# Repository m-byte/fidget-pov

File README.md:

# fidgethw
https://hackaday.io/project/25372-iot-pov-fidget-spinner

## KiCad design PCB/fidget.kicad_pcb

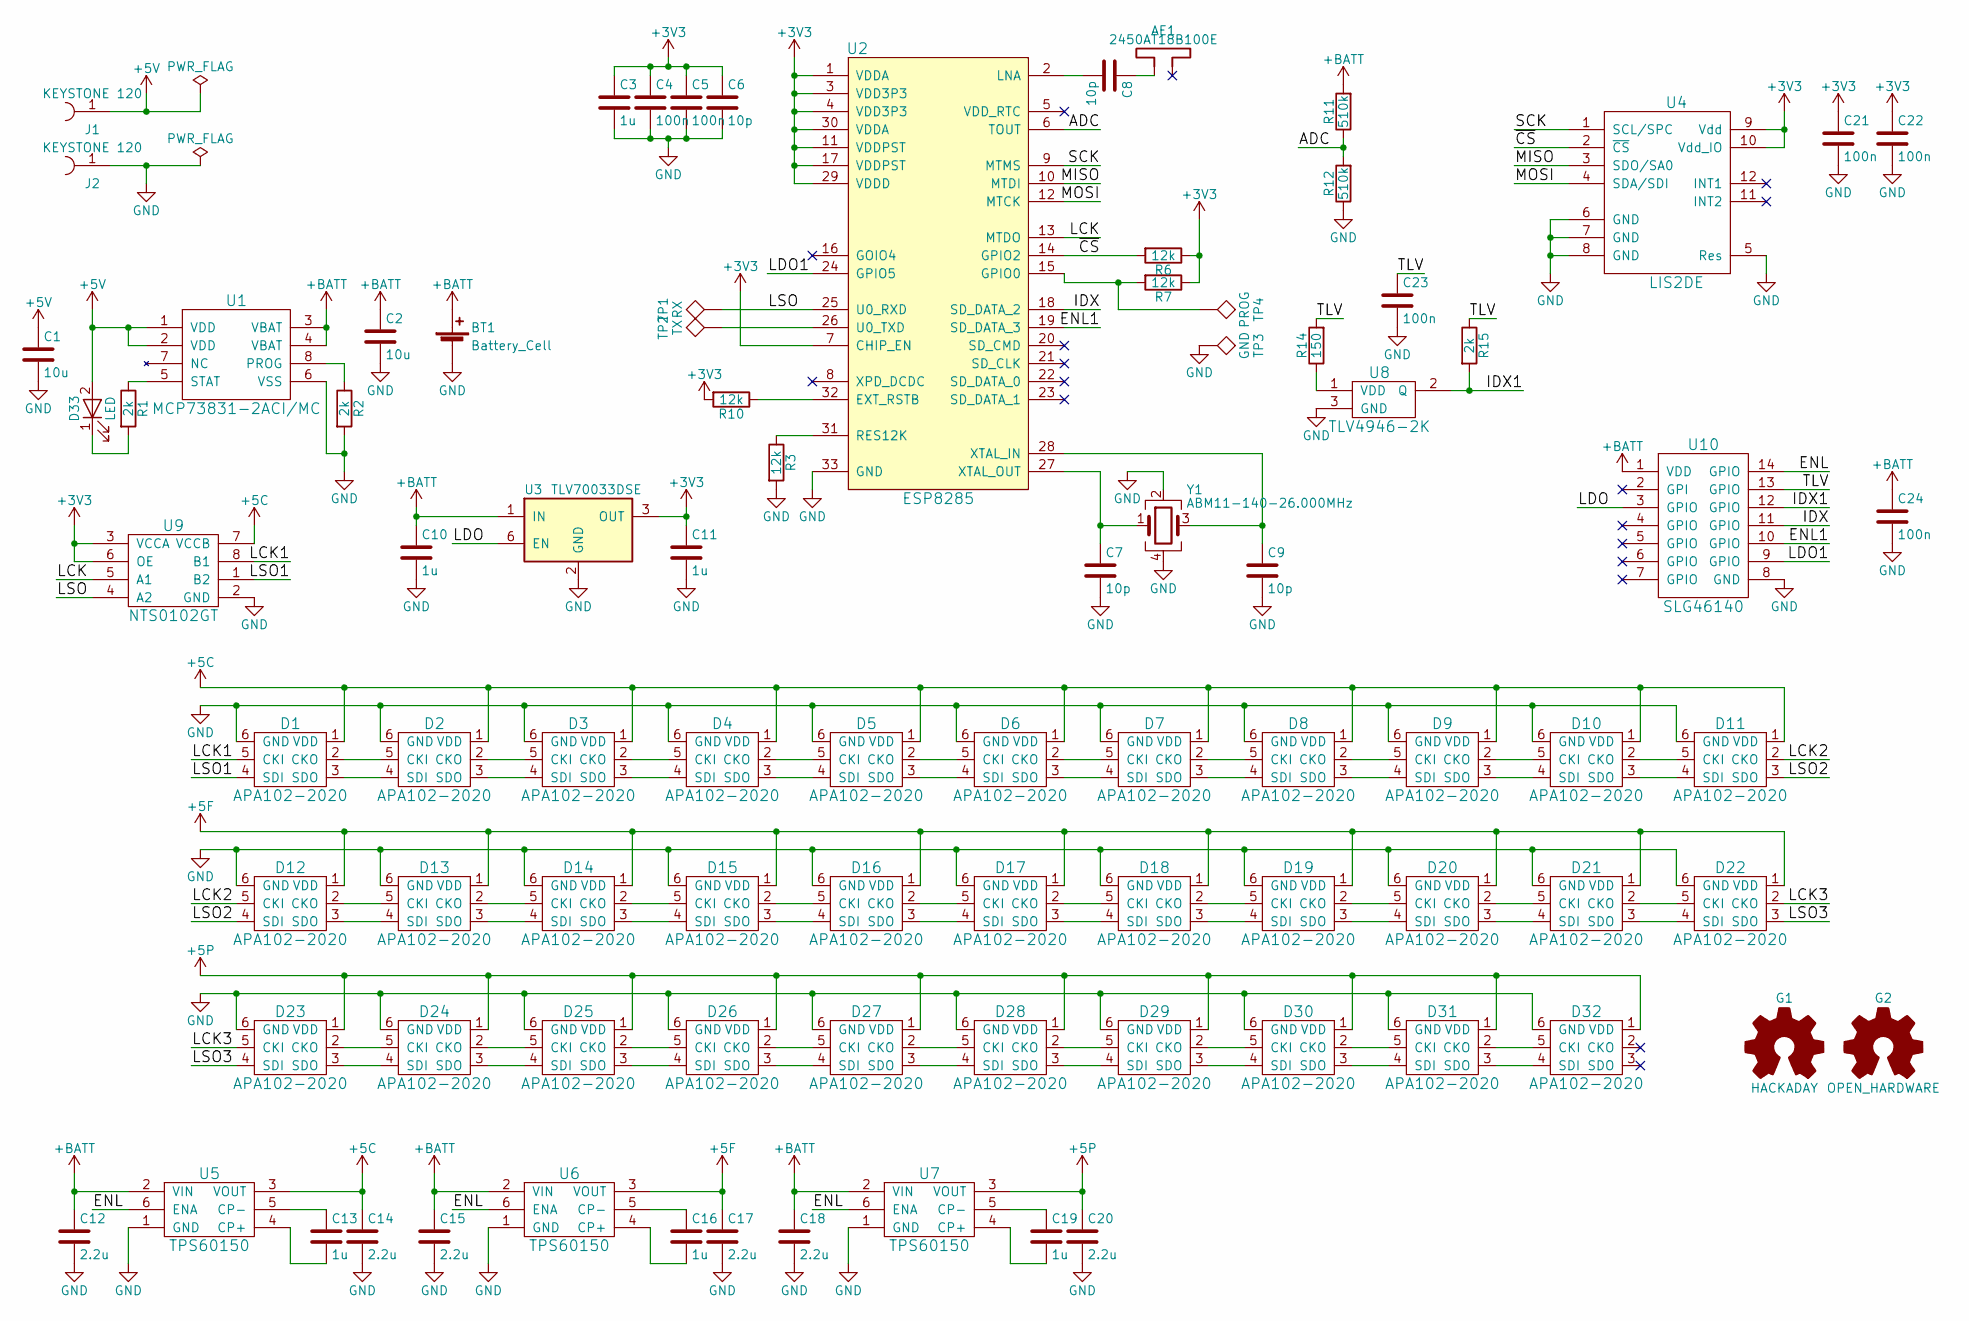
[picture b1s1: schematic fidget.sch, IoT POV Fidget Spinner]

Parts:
AE1: 2450AT18B100E; SMD-1206_Pol
BT1: Battery_Cell; Pin_Header_Straight_1x02_Pitch2.00mm
C1, C2: 10u; C_0603
C3, C10, C11: 1u; C_0402
C4, C5, C21, C22, C23, C24: 100n; C_0402
C6, C7, C8, C9: 10p; C_0402
C12, C14, C15, C17, C18, C20: 2.2u; C_0603
C13, C16, C19: 1u; C_0603
D1, D2, D3, D4, D5, D6, D7, D8, D9, D10, D11, D12, D13, D14, D15, D16, D17, D18, D19, D20, D21, D22, D23, D24, D25, D26, D27, D28, D29, D30, D31, D32: APA102-2020; LED_APA102-2020
D33: LED; LED_0805
G1: HACKADAY; wrencher_8mm
G2: OPEN_HARDWARE; OSHW-Logo_7.5x8mm_SilkScreen
J1, J2: KEYSTONE 120; Keystone_120_19mm
R1, R2, R15: 2k; R_0402
R3, R6, R7, R10: 12k; R_0402
R11, R12: 510k; R_0402
R14: 150; R_0402
TP1: RX; Measurement_Point_Round-SMD-Pad_Small
TP2: TX; Measurement_Point_Round-SMD-Pad_Small
TP3: GND; Measurement_Point_Round-SMD-Pad_Small
TP4: PROG; Measurement_Point_Round-SMD-Pad_Small
U1: MCP73831-2ACI/MC; DFN-8-1EP_3x2mm_Pitch0.5mm
U2: ESP8285; QFN-32-1EP_5x5mm_Pitch0.5mm
U3: TLV70033DSE; WSON6_1.5x1.5mm_Pitch0.5mm
U4: LIS2DE; LGA-12_2x2mm_Pitch0.5mm
U5, U6, U7: TPS60150; DFN-6-1EP_2x2mm_Pitch0.65mm
U8: TLV4946-2K; SC-59
U9: NTS0102GT; SOT833-1
U10: SLG46140; SILEGO_STQFN-14L-1.6x2mm_Pitch0.4mm
Y1: ABM11-140-26.000MHz; Crystal_SMD_2016-4pin_2.0x1.6mm

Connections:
+3V3: C3.1, C4.1, C5.1, C6.1, C11.1, C21.1, C22.1, R6.1, R7.1, R10.2, U2.1 (VDDA), U2.3 (VDD3P3), U2.4 (VDD3P3), U2.7 (CHIP_EN), U2.11 (VDDPST), U2.17 (VDDPST), U2.29 (VDDD), U2.30 (VDDA), U3.3 (OUT), U4.9 (Vdd), U4.10 (Vdd_IO), U9.3 (VCCA), U9.6 (OE)
+5C: C14.1, D1.1 (VDD), D2.1 (VDD), D3.1 (VDD), D4.1 (VDD), D5.1 (VDD), D6.1 (VDD), D7.1 (VDD), D8.1 (VDD), D9.1 (VDD), D10.1 (VDD), D11.1 (VDD), U5.3 (VOUT), U9.7 (VCCB)
+5F: C17.1, D12.1 (VDD), D13.1 (VDD), D14.1 (VDD), D15.1 (VDD), D16.1 (VDD), D17.1 (VDD), D18.1 (VDD), D19.1 (VDD), D20.1 (VDD), D21.1 (VDD), D22.1 (VDD), U6.3 (VOUT)
+5P: C20.1, D23.1 (VDD), D24.1 (VDD), D25.1 (VDD), D26.1 (VDD), D27.1 (VDD), D28.1 (VDD), D29.1 (VDD), D30.1 (VDD), D31.1 (VDD), D32.1 (VDD), U7.3 (VOUT)
+5V: C1.1, D33.2 (A), J1.1, U1.1 (VDD), U1.2 (VDD)
+BATT: BT1.1 (+), C2.1, C10.1, C12.1, C15.1, C18.1, C24.1, R11.2, U1.3 (VBAT), U1.4 (VBAT), U3.1 (IN), U5.2 (VIN), U6.2 (VIN), U7.2 (VIN), U10.1 (VDD)
/ADC: R11.1, R12.2, U2.6 (TOUT)
/ENL: U5.6 (ENA), U6.6 (ENA), U7.6 (ENA), U10.14 (GPIO)
/ENL1: U2.19 (SD_DATA_3), U10.10 (GPIO)
/IDX: U2.18 (SD_DATA_2), U10.11 (GPIO)
/IDX1: R15.2, U8.2 (Q), U10.12 (GPIO)
/LCK: U2.13 (MTDO), U9.5 (A1)
/LCK1: D1.5 (CKI), U9.8 (B1)
/LCK2: D11.2 (CKO), D12.5 (CKI)
/LCK3: D22.2 (CKO), D23.5 (CKI)
/LDO: U3.6 (EN), U10.3 (GPIO)
/LDO1: U2.24 (GPIO5), U10.9 (GPIO)
/LSO: TP1.1, U2.25 (U0_RXD), U9.4 (A2)
/LSO1: D1.4 (SDI), U9.1 (B2)
/LSO2: D11.3 (SDO), D12.4 (SDI)
/LSO3: D22.3 (SDO), D23.4 (SDI)
/MISO: U2.10 (MTDI), U4.3 (SDO/SA0)
/MOSI: U2.12 (MTCK), U4.4 (SDA/SDI)
/SCK: U2.9 (MTMS), U4.1 (SCL/SPC)
/TLV: C23.1, R14.2, R15.1, U10.13 (GPIO)
/~CS~: R6.2, U2.14 (GPIO2), U4.2 (~CS~)
GND: BT1.2 (-), C1.2, C2.2, C3.2, C4.2, C5.2, C6.2, C7.2, C9.2, C10.2, C11.2, C12.2, C14.2, C15.2, C17.2, C18.2, C20.2, C21.2, C22.2, C23.2, C24.2, D1.6 (GND), D2.6 (GND), D3.6 (GND), D4.6 (GND), D5.6 (GND), D6.6 (GND), D7.6 (GND), D8.6 (GND), D9.6 (GND), D10.6 (GND), D11.6 (GND), D12.6 (GND), D13.6 (GND), D14.6 (GND), D15.6 (GND), D16.6 (GND), D17.6 (GND), D18.6 (GND), D19.6 (GND), D20.6 (GND), D21.6 (GND), D22.6 (GND), D23.6 (GND), D24.6 (GND), D25.6 (GND), D26.6 (GND), D27.6 (GND), D28.6 (GND), D29.6 (GND), D30.6 (GND), D31.6 (GND), D32.6 (GND), J2.1, R2.2, R3.2, R12.1, TP3.1, U1.6 (VSS), U2.33 (GND), U3.2 (GND), U4.5 (Res), U4.6 (GND), U4.7 (GND), U4.8 (GND), U5.1 (GND), U6.1 (GND), U7.1 (GND), U8.3 (GND), U9.2 (GND), U10.8 (GND), Y1.2, Y1.4
unnamed: AE1.1, C8.1
unnamed: C7.1, U2.27 (XTAL_OUT), Y1.1
unnamed: C8.2, U2.2 (LNA)
unnamed: C9.1, U2.28 (XTAL_IN), Y1.3
unnamed: C13.1, U5.5 (CP-)
unnamed: C13.2, U5.4 (CP+)
unnamed: C16.1, U6.5 (CP-)
unnamed: C16.2, U6.4 (CP+)
unnamed: C19.1, U7.5 (CP-)
unnamed: C19.2, U7.4 (CP+)
unnamed: D1.2 (CKO), D2.5 (CKI)
unnamed: D1.3 (SDO), D2.4 (SDI)
unnamed: D2.2 (CKO), D3.5 (CKI)
unnamed: D2.3 (SDO), D3.4 (SDI)
unnamed: D3.2 (CKO), D4.5 (CKI)
unnamed: D3.3 (SDO), D4.4 (SDI)
unnamed: D4.2 (CKO), D5.5 (CKI)
unnamed: D4.3 (SDO), D5.4 (SDI)
unnamed: D5.2 (CKO), D6.5 (CKI)
unnamed: D5.3 (SDO), D6.4 (SDI)
unnamed: D6.2 (CKO), D7.5 (CKI)
unnamed: D6.3 (SDO), D7.4 (SDI)
unnamed: D7.2 (CKO), D8.5 (CKI)
unnamed: D7.3 (SDO), D8.4 (SDI)
unnamed: D8.2 (CKO), D9.5 (CKI)
unnamed: D8.3 (SDO), D9.4 (SDI)
unnamed: D10.2 (CKO), D11.5 (CKI)
unnamed: D10.3 (SDO), D11.4 (SDI)
unnamed: D9.3 (SDO), D10.4 (SDI)
unnamed: D9.2 (CKO), D10.5 (CKI)
unnamed: D12.2 (CKO), D13.5 (CKI)
unnamed: D12.3 (SDO), D13.4 (SDI)
unnamed: D13.2 (CKO), D14.5 (CKI)
unnamed: D13.3 (SDO), D14.4 (SDI)
unnamed: D14.2 (CKO), D15.5 (CKI)
unnamed: D14.3 (SDO), D15.4 (SDI)
unnamed: D15.2 (CKO), D16.5 (CKI)
unnamed: D15.3 (SDO), D16.4 (SDI)
unnamed: D16.2 (CKO), D17.5 (CKI)
unnamed: D16.3 (SDO), D17.4 (SDI)
unnamed: D17.2 (CKO), D18.5 (CKI)
unnamed: D17.3 (SDO), D18.4 (SDI)
unnamed: D18.2 (CKO), D19.5 (CKI)
unnamed: D18.3 (SDO), D19.4 (SDI)
unnamed: D19.2 (CKO), D20.5 (CKI)
unnamed: D19.3 (SDO), D20.4 (SDI)
unnamed: D20.2 (CKO), D21.5 (CKI)
unnamed: D20.3 (SDO), D21.4 (SDI)
unnamed: D21.2 (CKO), D22.5 (CKI)
unnamed: D21.3 (SDO), D22.4 (SDI)
unnamed: D23.2 (CKO), D24.5 (CKI)
unnamed: D23.3 (SDO), D24.4 (SDI)
unnamed: D24.2 (CKO), D25.5 (CKI)
unnamed: D24.3 (SDO), D25.4 (SDI)
unnamed: D25.2 (CKO), D26.5 (CKI)
unnamed: D25.3 (SDO), D26.4 (SDI)
unnamed: D26.2 (CKO), D27.5 (CKI)
unnamed: D26.3 (SDO), D27.4 (SDI)
unnamed: D27.2 (CKO), D28.5 (CKI)
unnamed: D27.3 (SDO), D28.4 (SDI)
unnamed: D28.2 (CKO), D29.5 (CKI)
unnamed: D28.3 (SDO), D29.4 (SDI)
unnamed: D29.2 (CKO), D30.5 (CKI)
unnamed: D29.3 (SDO), D30.4 (SDI)
unnamed: D30.2 (CKO), D31.5 (CKI)
unnamed: D30.3 (SDO), D31.4 (SDI)
unnamed: D31.2 (CKO), D32.5 (CKI)
unnamed: D31.3 (SDO), D32.4 (SDI)
unnamed: D33.1 (K), R1.2
unnamed: R1.1, U1.5 (STAT)
unnamed: R2.1, U1.8 (PROG)
unnamed: R3.1, U2.31 (RES12K)
unnamed: R7.2, TP4.1, U2.15 (GPIO0)
unnamed: R10.1, U2.32 (EXT_RSTB)
unnamed: R14.1, U8.1 (VDD)
unnamed: TP2.1, U2.26 (U0_TXD)

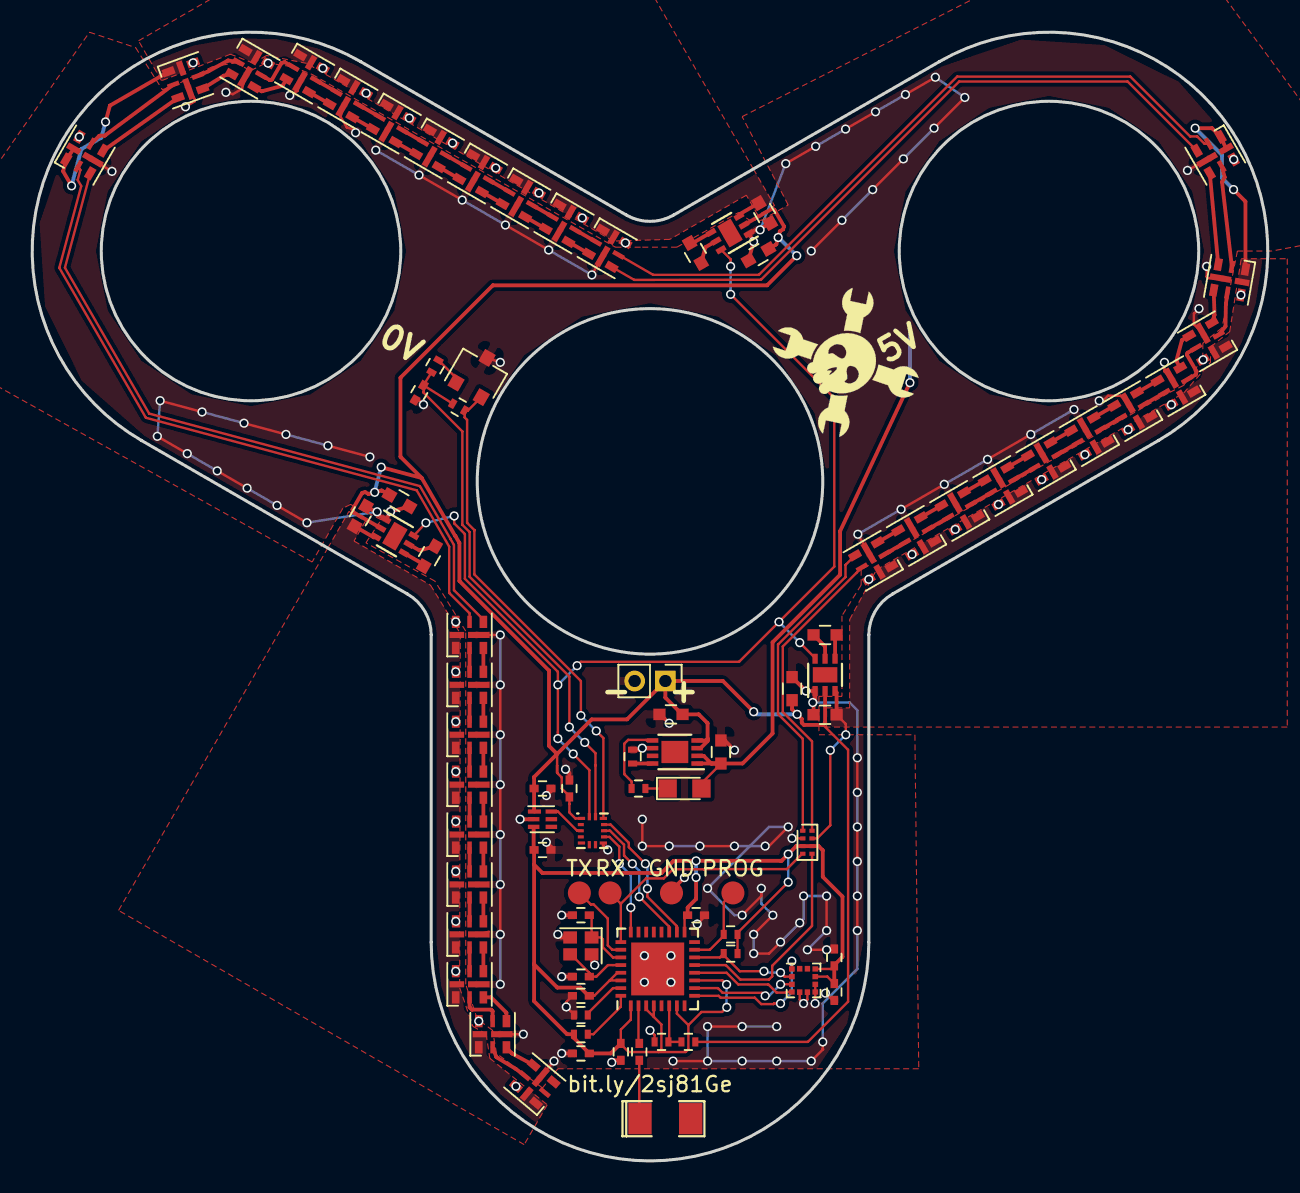
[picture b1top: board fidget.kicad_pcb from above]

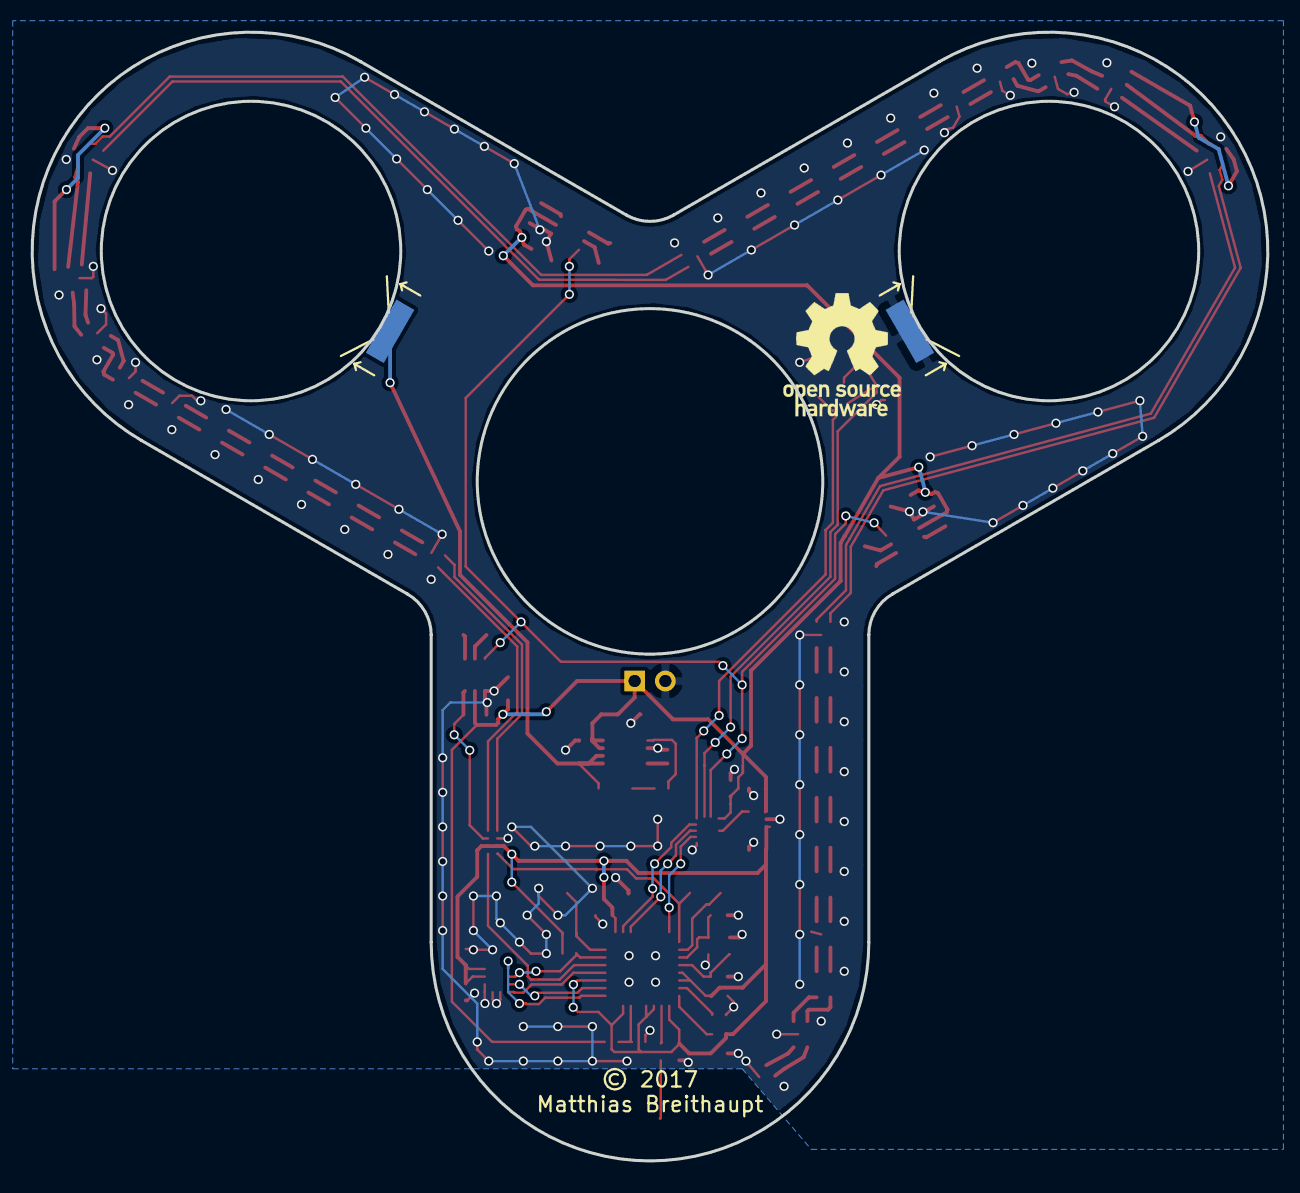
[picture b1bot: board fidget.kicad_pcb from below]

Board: 2 copper layers, 80.5 x 73.5 mm, 88 parts (3 on the bottom side), 103 nets.

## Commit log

2017-06-09 schematic done
2017-06-10 PCB design at 4am.. probably a bad idea
2017-06-10 RTFM: reverse polarity protection is already inside MCP73831
2017-06-10 routing done
2017-06-10 cleaned up silkscreen
2017-06-11 added scad file
2017-06-11 added level shifter
2017-06-13 switched to hall sensor
2017-06-13 added SLG46140 for UVLO and power management
2017-06-13 Changed file structure
2017-06-13 moved hall sensor to battery rail so it can work with the LDO powered off
2017-06-13 fixed greenpak configuration
2017-06-13 added text to silkscreen
2017-06-13 control power to hall sensor from pld
2017-06-14 increase center hole to 608 size - outer bearings are still 626
2017-06-14 fixed silkscreen

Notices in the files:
PCB/fidget.kicad_pcb:
© 2017
